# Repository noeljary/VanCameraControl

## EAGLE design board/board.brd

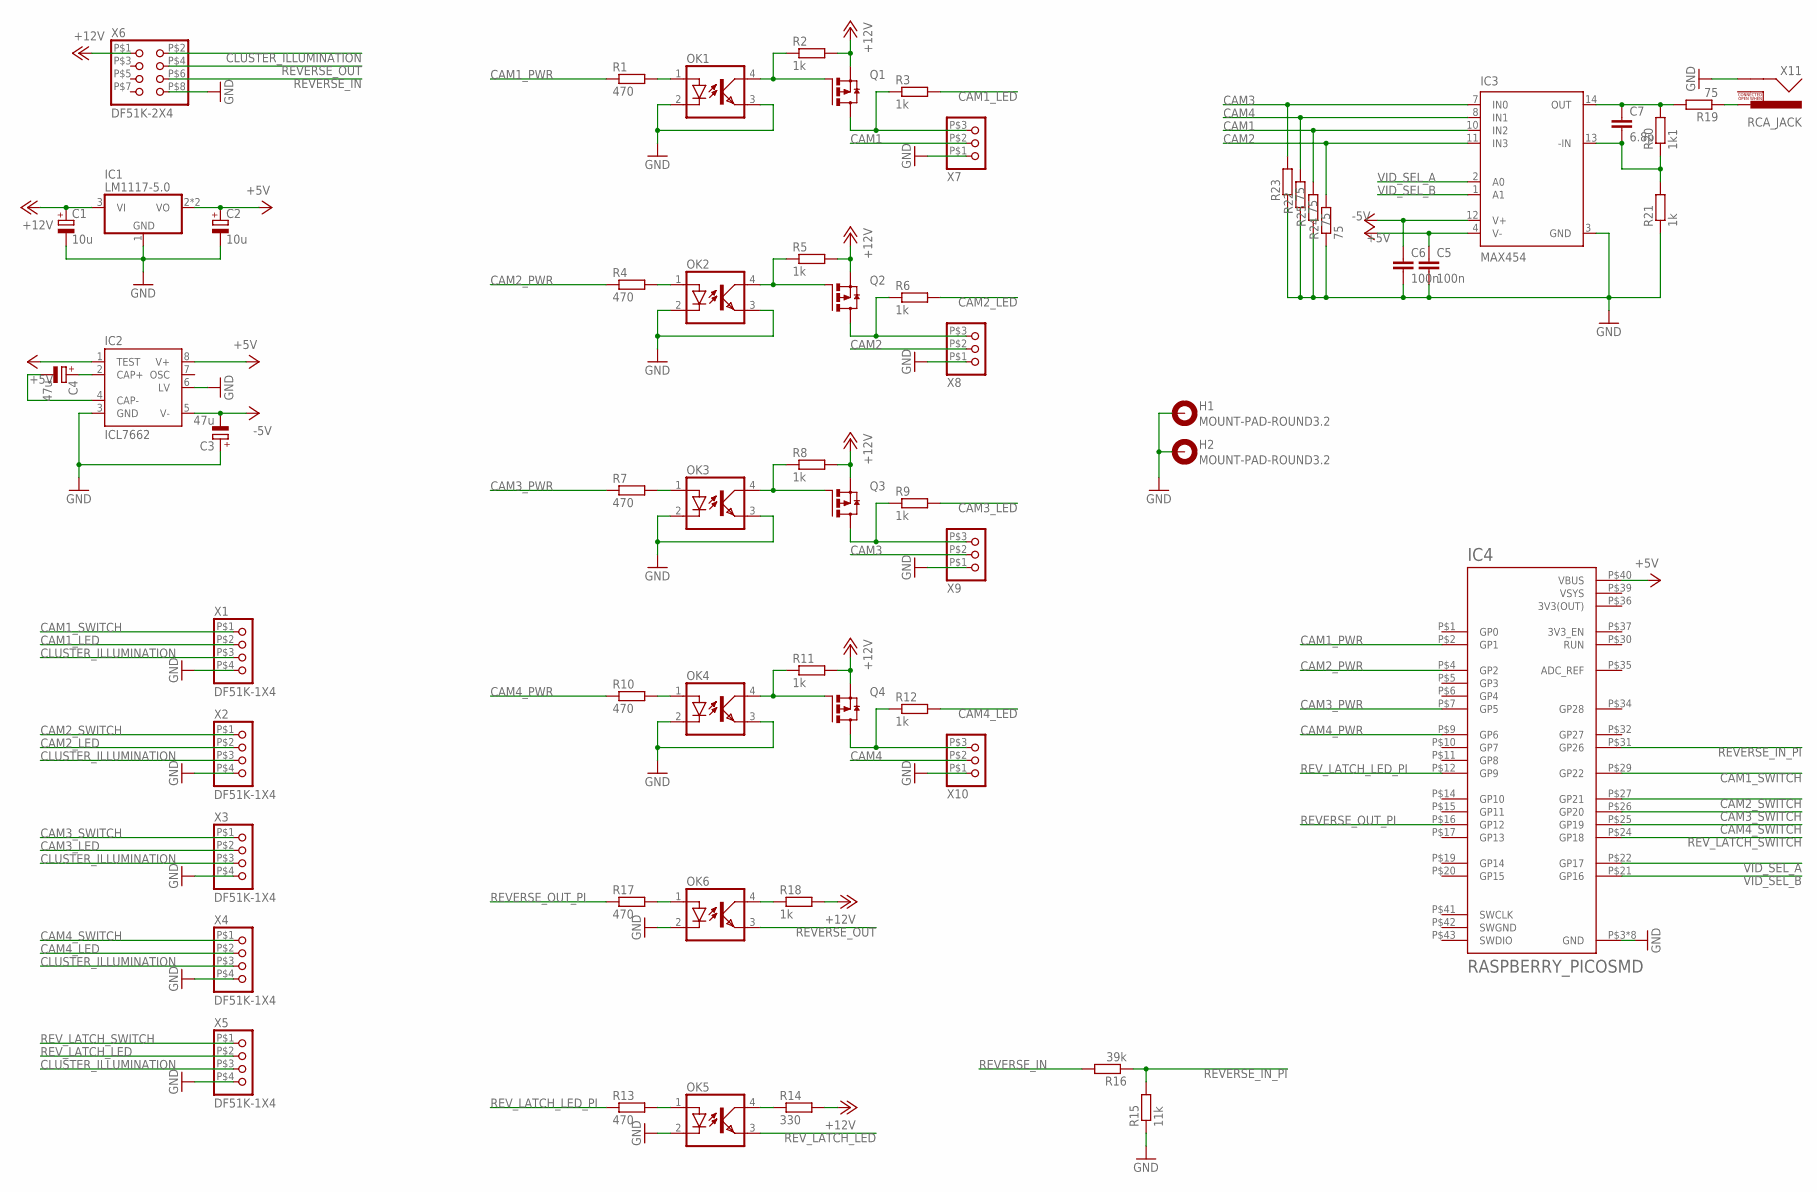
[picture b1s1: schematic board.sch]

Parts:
C1, C2: 10u; C_4MM
C3, C4: 47u; CT7343
C5, C6: 100n; C0805
C7: 6.8p; C0805
H1, H2: MOUNT-PAD-ROUND3.2; 3,2-PAD
IC1: LM1117-5.0; SOT223
IC2: ICL7662; SO08
IC3: MAX454; DIL14
IC4: RASPBERRY_PICOSMD; PICO-PKG-SMD
OK1, OK2, OK3, OK4, OK5, OK6: OPTOCOUPLERSO4; SO04
Q1, Q2, Q3, Q4: MOSFET_P_CHANNELSOT23; SOT23
R1, R4, R7, R10, R13, R17: 470; R0805
R2, R3, R5, R6, R8, R9, R11, R12, R18, R21: 1k; R0805
R14: 330; R0805
R15: 11k; R0805
R16: 39k; R0805
R19, R22, R23, R24, R25: 75; R0805
R20: 1k1; R0805
X1, X2, X3, X4, X5: DF51K-1X4
X6: DF51K-2X4
X7, X8, X9, X10: JST_XH_1X3
X11: RCA_JACK

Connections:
3V3(OUT): IC4.P$36 (3V3(OUT))
+5V: C2.+, C6.1, IC1.2 (VO), IC1.4 (VO), IC2.1 (TEST), IC2.8 (V+), IC3.12 (V+), IC4.P$40 (VBUS)
+12V: C1.+, IC1.3 (VI), Q1.2 (S), Q2.2 (S), Q3.2 (S), Q4.2 (S), R2.2, R5.2, R8.2, R11.2, R14.2, R18.2, X6.P$1 (1)
-5V: C3.-, C5.1, IC2.5 (V-), IC3.4 (V-)
CAM1: IC3.10 (IN2), R25.2, X7.P$2 (2)
CAM1_LED: R3.2, X1.P$2 (2)
CAM1_PWR: IC4.P$2 (GP1), R1.1
CAM1_SWITCH: IC4.P$29 (GP22), X1.P$1 (1)
CAM2: IC3.11 (IN3), R24.2, X8.P$2 (2)
CAM2_LED: R6.2, X2.P$2 (2)
CAM2_PWR: IC4.P$4 (GP2), R4.1
CAM2_SWITCH: IC4.P$27 (GP21), X2.P$1 (1)
CAM3: IC3.7 (IN0), R23.2, X9.P$2 (2)
CAM3_LED: R9.2, X3.P$2 (2)
CAM3_PWR: IC4.P$7 (GP5), R7.1
CAM3_SWITCH: IC4.P$26 (GP20), X3.P$1 (1)
CAM4: IC3.8 (IN1), R22.2, X10.P$2 (2)
CAM4_LED: R12.2, X4.P$2 (2)
CAM4_PWR: IC4.P$9 (GP6), R10.1
CAM4_SWITCH: IC4.P$25 (GP19), X4.P$1 (1)
CLUSTER_ILLUMINATION: X1.P$3 (3), X2.P$3 (3), X3.P$3 (3), X4.P$3 (3), X5.P$3 (3), X6.P$2 (2)
GND: C1.-, C2.-, C3.+, C5.2, C6.2, H1.B3,2, H1.P$1, H1.P$2, H1.P$3, H1.P$4, H1.P$5, H1.P$6, H1.P$7, H1.P$8, H2.B3,2, H2.P$1, H2.P$2, H2.P$3, H2.P$4, H2.P$5, H2.P$6, H2.P$7, H2.P$8, IC1.1 (GND), IC2.3 (GND), IC2.6 (LV), IC3.3 (GND), IC4.P$3 (GND), IC4.P$8 (GND), IC4.P$13 (GND), IC4.P$18 (GND), IC4.P$23 (GND), IC4.P$28 (GND), IC4.P$33 (GND), IC4.P$38 (GND), OK1.2 (C), OK1.3 (EMIT), OK2.2 (C), OK2.3 (EMIT), OK3.2 (C), OK3.3 (EMIT), OK4.2 (C), OK4.3 (EMIT), OK5.2 (C), OK6.2 (C), R15.1, R21.1, R22.1, R23.1, R24.1, R25.1, X1.P$4 (4), X2.P$4 (4), X3.P$4 (4), X4.P$4 (4), X5.P$4 (4), X6.P$8 (8), X7.P$1 (1), X8.P$1 (1), X9.P$1 (1), X10.P$1 (1), X11.1 (SHELL)
unnamed: C4.+, IC2.2 (CAP+)
unnamed: C4.-, IC2.4 (CAP-)
unnamed: OK1.1 (A), R1.2
unnamed: OK1.4 (COL), Q1.1 (G), R2.1
unnamed: Q1.3 (D), R3.1, X7.P$3 (3)
unnamed: OK2.1 (A), R4.2
unnamed: OK2.4 (COL), Q2.1 (G), R5.1
unnamed: Q2.3 (D), R6.1, X8.P$3 (3)
unnamed: OK3.1 (A), R7.2
unnamed: OK3.4 (COL), Q3.1 (G), R8.1
unnamed: Q3.3 (D), R9.1, X9.P$3 (3)
unnamed: OK4.1 (A), R10.2
unnamed: C7.1, IC3.14 (OUT), R19.2, R20.2
unnamed: R19.1, X11.3 (PIN)
unnamed: C7.2, IC3.13 (-IN), R20.1, R21.2
unnamed: OK4.4 (COL), Q4.1 (G), R11.1
unnamed: Q4.3 (D), R12.1, X10.P$3 (3)
unnamed: OK6.1 (A), R17.2
unnamed: OK6.4 (COL), R18.1
unnamed: OK5.1 (A), R13.2
unnamed: OK5.4 (COL), R14.1
REVERSE_IN: R16.2, X6.P$6 (6)
REVERSE_IN_PI: IC4.P$31 (GP26), R15.2, R16.1
REVERSE_OUT: OK6.3 (EMIT), X6.P$4 (4)
REVERSE_OUT_PI: IC4.P$16 (GP12), R17.1
REV_LATCH_LED: OK5.3 (EMIT), X5.P$2 (2)
REV_LATCH_LED_PI: IC4.P$12 (GP9), R13.1
REV_LATCH_SWITCH: IC4.P$24 (GP18), X5.P$1 (1)
SWGND: IC4.P$42 (SWGND)
VID_SEL_A: IC3.2 (A0), IC4.P$22 (GP17)
VID_SEL_B: IC3.1 (A1), IC4.P$21 (GP16)
VSYS: IC4.P$39 (VSYS)

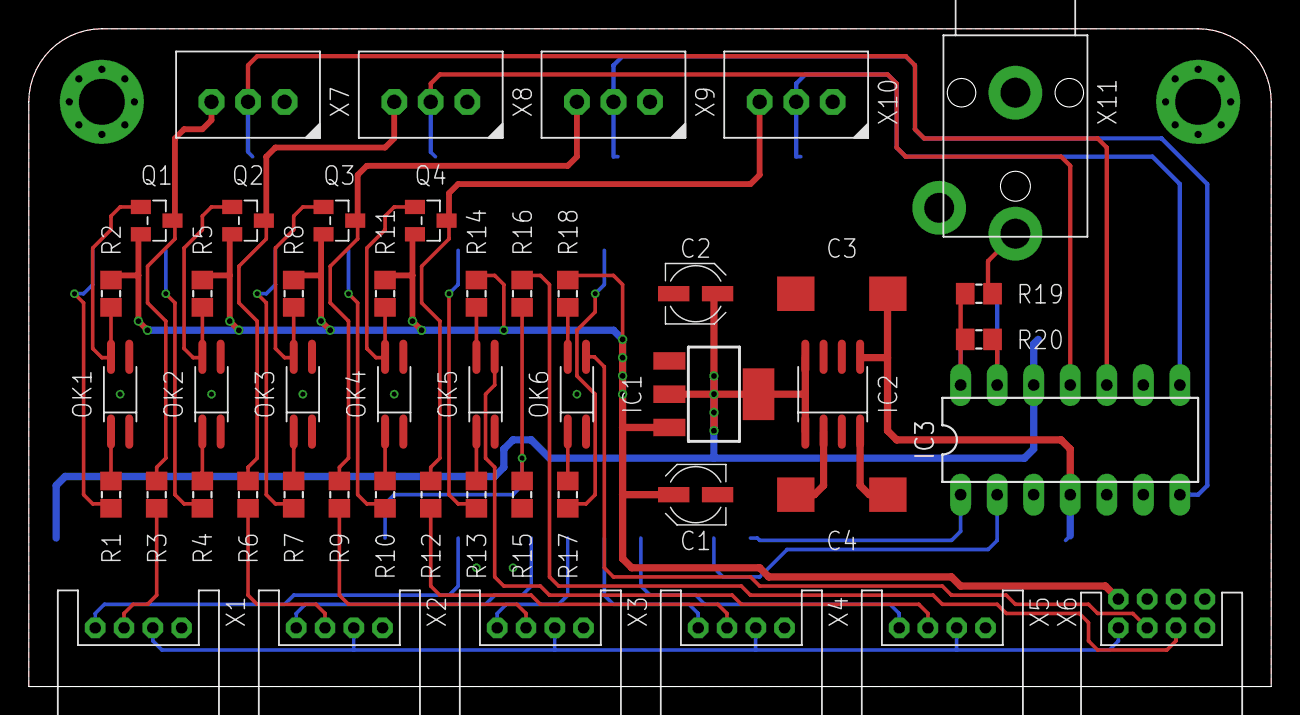
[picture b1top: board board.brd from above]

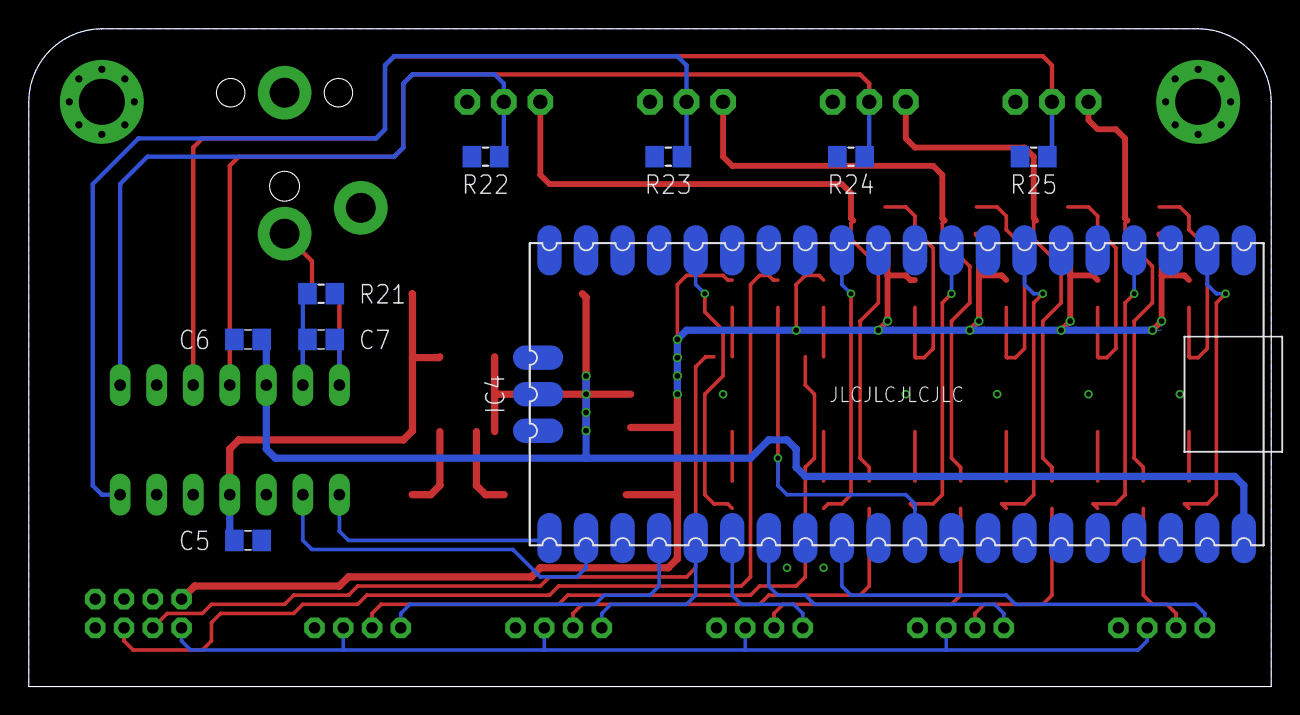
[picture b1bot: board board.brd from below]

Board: 2 copper layers, 86.4 x 45.7 mm, 59 parts (9 on the bottom side), 51 nets.

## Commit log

2022-11-26 Add Van Camera Control System into Git
2022-11-27 Updated code with latest revision from device testing
